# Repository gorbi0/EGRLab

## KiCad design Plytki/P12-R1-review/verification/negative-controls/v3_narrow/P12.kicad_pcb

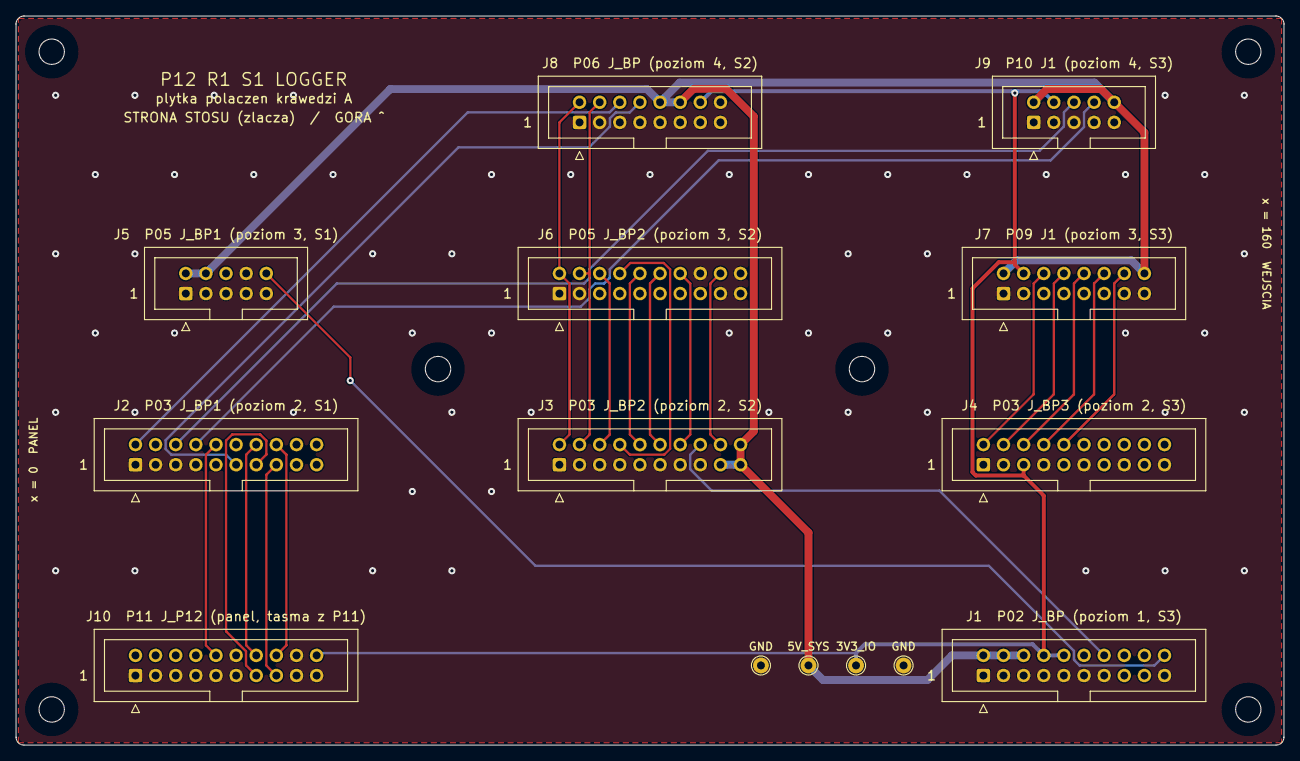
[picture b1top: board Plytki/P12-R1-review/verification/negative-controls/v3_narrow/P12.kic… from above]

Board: 2 copper layers, 160.0 x 92.0 mm, 20 parts (0 on the bottom side), 27 nets.

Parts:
H1, H2, H3, H4, H5, H6: M3 NPTH
J1: P02 J_BP; IDC-Header_2x10_P2.54mm_Vertical
J2: P03 J_BP1; IDC-Header_2x10_P2.54mm_Vertical
J3: P03 J_BP2; IDC-Header_2x10_P2.54mm_Vertical
J4: P03 J_BP3; IDC-Header_2x10_P2.54mm_Vertical
J5: P05 J_BP1; IDC-Header_2x05_P2.54mm_Vertical
J6: P05 J_BP2; IDC-Header_2x10_P2.54mm_Vertical
J7: P09 J1; IDC-Header_2x08_P2.54mm_Vertical
J8: P06 J_BP; IDC-Header_2x08_P2.54mm_Vertical
J9: P10 J1; IDC-Header_2x05_P2.54mm_Vertical
J10: P11 J_P12; IDC-Header_2x10_P2.54mm_Vertical
TP1, TP4: GND; TestPoint_THTPad_D2.0mm_Drill1.0mm
TP2: 5V_SYS; TestPoint_THTPad_D2.0mm_Drill1.0mm
TP3: 3V3_IO; TestPoint_THTPad_D2.0mm_Drill1.0mm

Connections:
3V3_IO: J1.8, J1.10, J4.5, J7.4, J8.14, J9.4, J10.20, TP3.1
5V_SYS: J1.2, J1.4, J1.6, J3.17, J3.19, J3.20, J5.2, J5.4, J7.2, J7.16, J8.10, J8.12, J9.2, J9.10, TP2.1
ADC_BUSY: J3.12, J6.12
ADC_CONVST: J3.10, J6.10
ADC_CS: J3.8, J6.8
ADC_DOUTA: J3.4, J6.4, J8.4
ADC_RESET: J3.18, J6.18
ADC_SCLK: J3.2, J6.2, J8.2
ADC_SDI: J3.6, J6.6
CAN_RX: J2.8, J9.8
CAN_TX: J2.6, J9.6
CS_ILOG_N: J2.2, J8.6
GND: J1.1, J1.3, J1.5, J1.7, J1.9, J1.11, J1.13, J1.19, J2.1, J2.3, J2.5, J2.7, J2.9, J3.1, J3.3, J3.5, J3.7, J3.9, J3.11, J3.13, J3.15, J4.1, J4.3, J4.7, J4.11, J4.15, J4.19, J5.1, J5.3, J5.5, J5.7, J5.8, J5.9, J6.1, J6.3, J6.5, J6.7, J6.9, J6.11, J6.13, J6.15, J6.16, J6.17, J6.19, J6.20, J7.1, J7.3, J7.5, J7.7, J7.9, J7.11, J7.13, J7.15, J8.1, J8.3, J8.5, J8.7, J8.9, J8.11, J8.13, J8.15, J8.16, J9.1, J9.3, J9.5, J9.7, J9.9, J10.1, J10.3, J10.5, J10.7, J10.9, J10.11, J10.12, J10.17, J10.18, J10.19, TP1.1, TP4.1
LOGGER_CLEAR: J2.15, J10.15
LOGGER_CURRENT_OK: J2.11, J8.8
MARK: J2.13, J10.13
MEAS_EN: J3.14, J6.14
N_J_SCOPE_HOT: J2.10, J10.10
PFAIL_N: J1.14, J3.16
SPI3_MISO: J4.6, J7.10
SPI3_MOSI: J4.4, J7.8
SPI3_SCLK: J4.2, J7.6
TC1_CS: J4.8, J7.12
TC2_CS: J4.10, J7.14
TEST_KEY: J2.14, J10.14
TEST_PRESENT: J2.16, J10.16
VBAT_SENSE: J1.20, J5.10

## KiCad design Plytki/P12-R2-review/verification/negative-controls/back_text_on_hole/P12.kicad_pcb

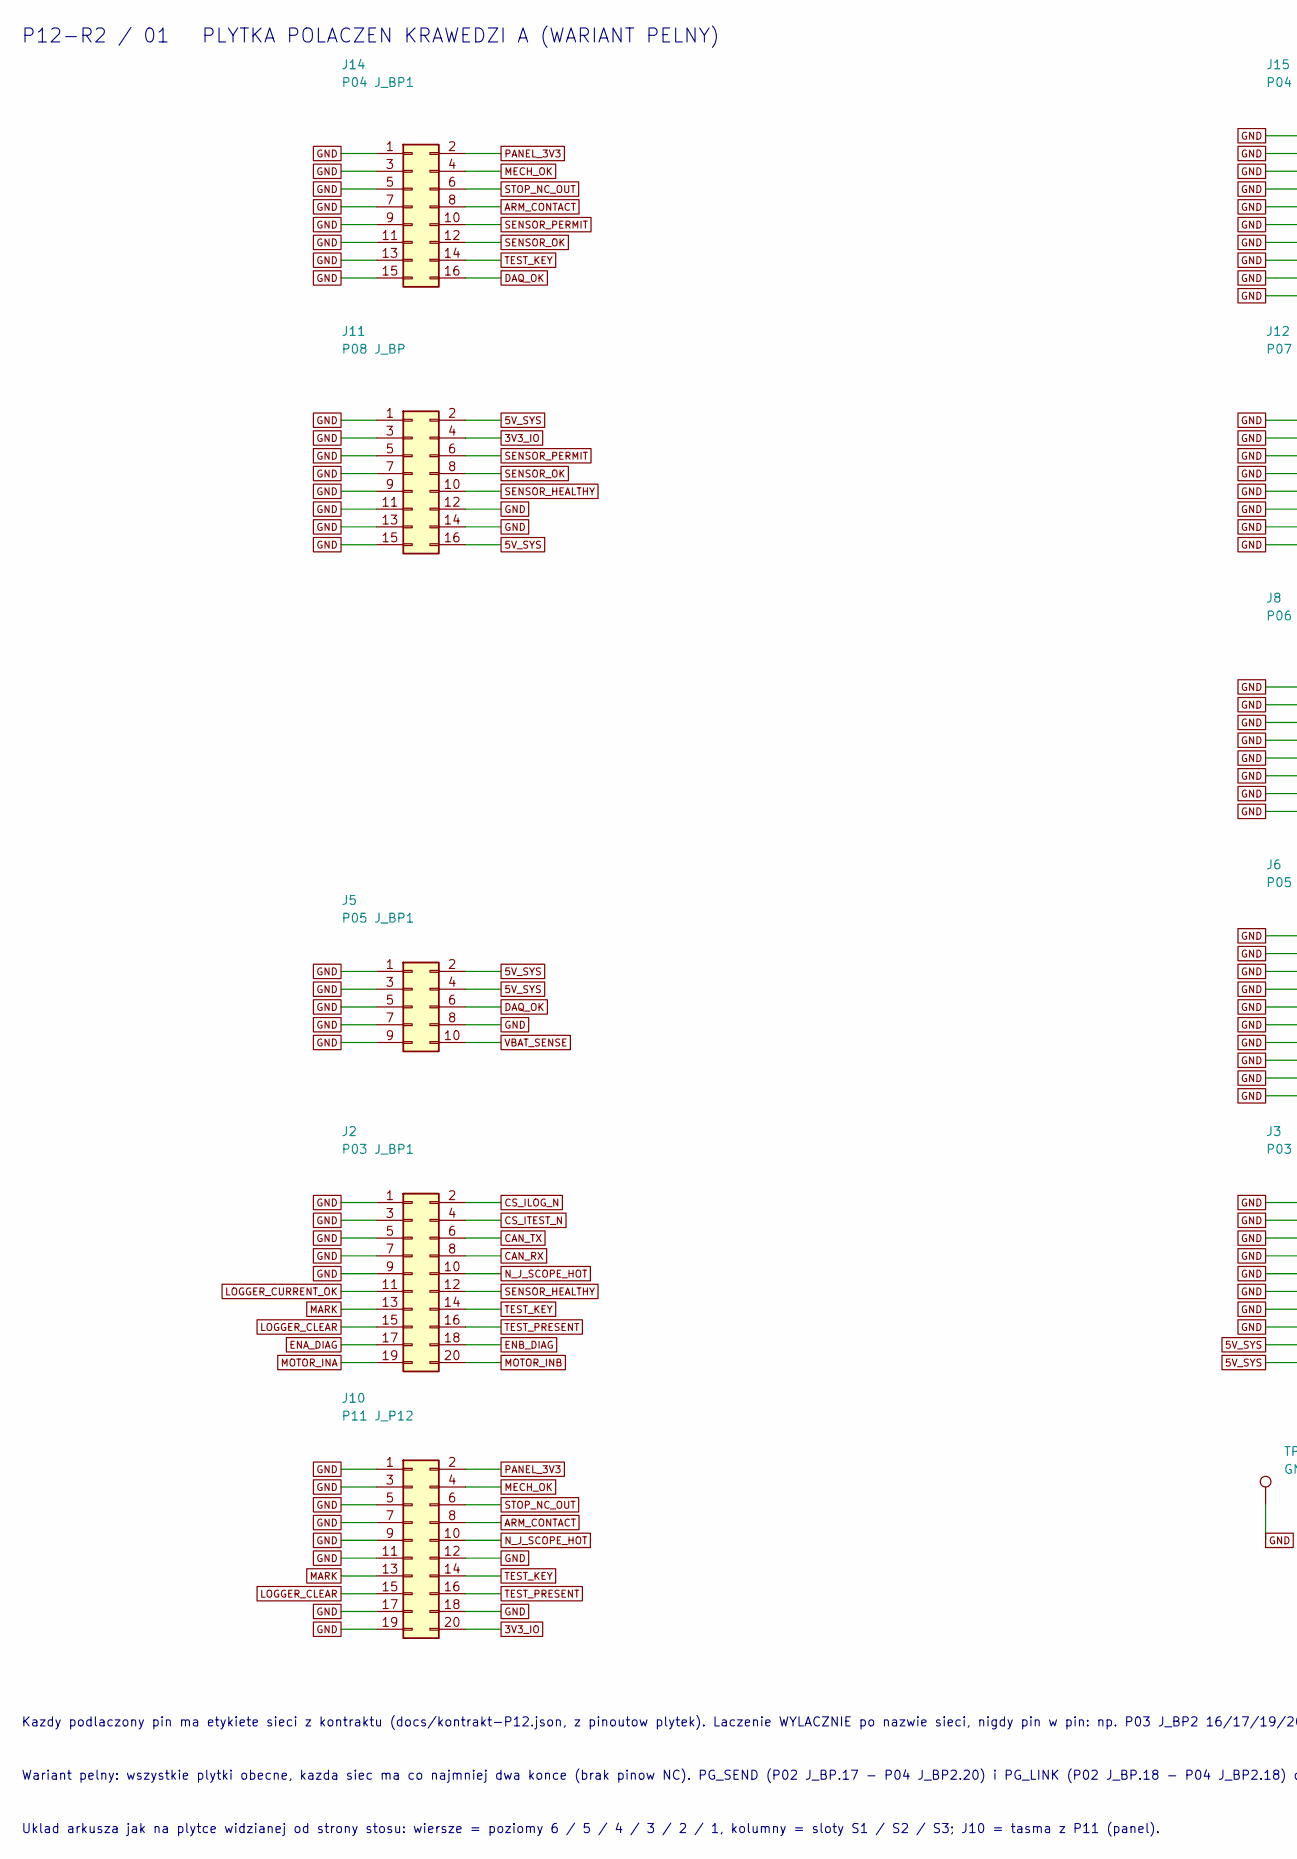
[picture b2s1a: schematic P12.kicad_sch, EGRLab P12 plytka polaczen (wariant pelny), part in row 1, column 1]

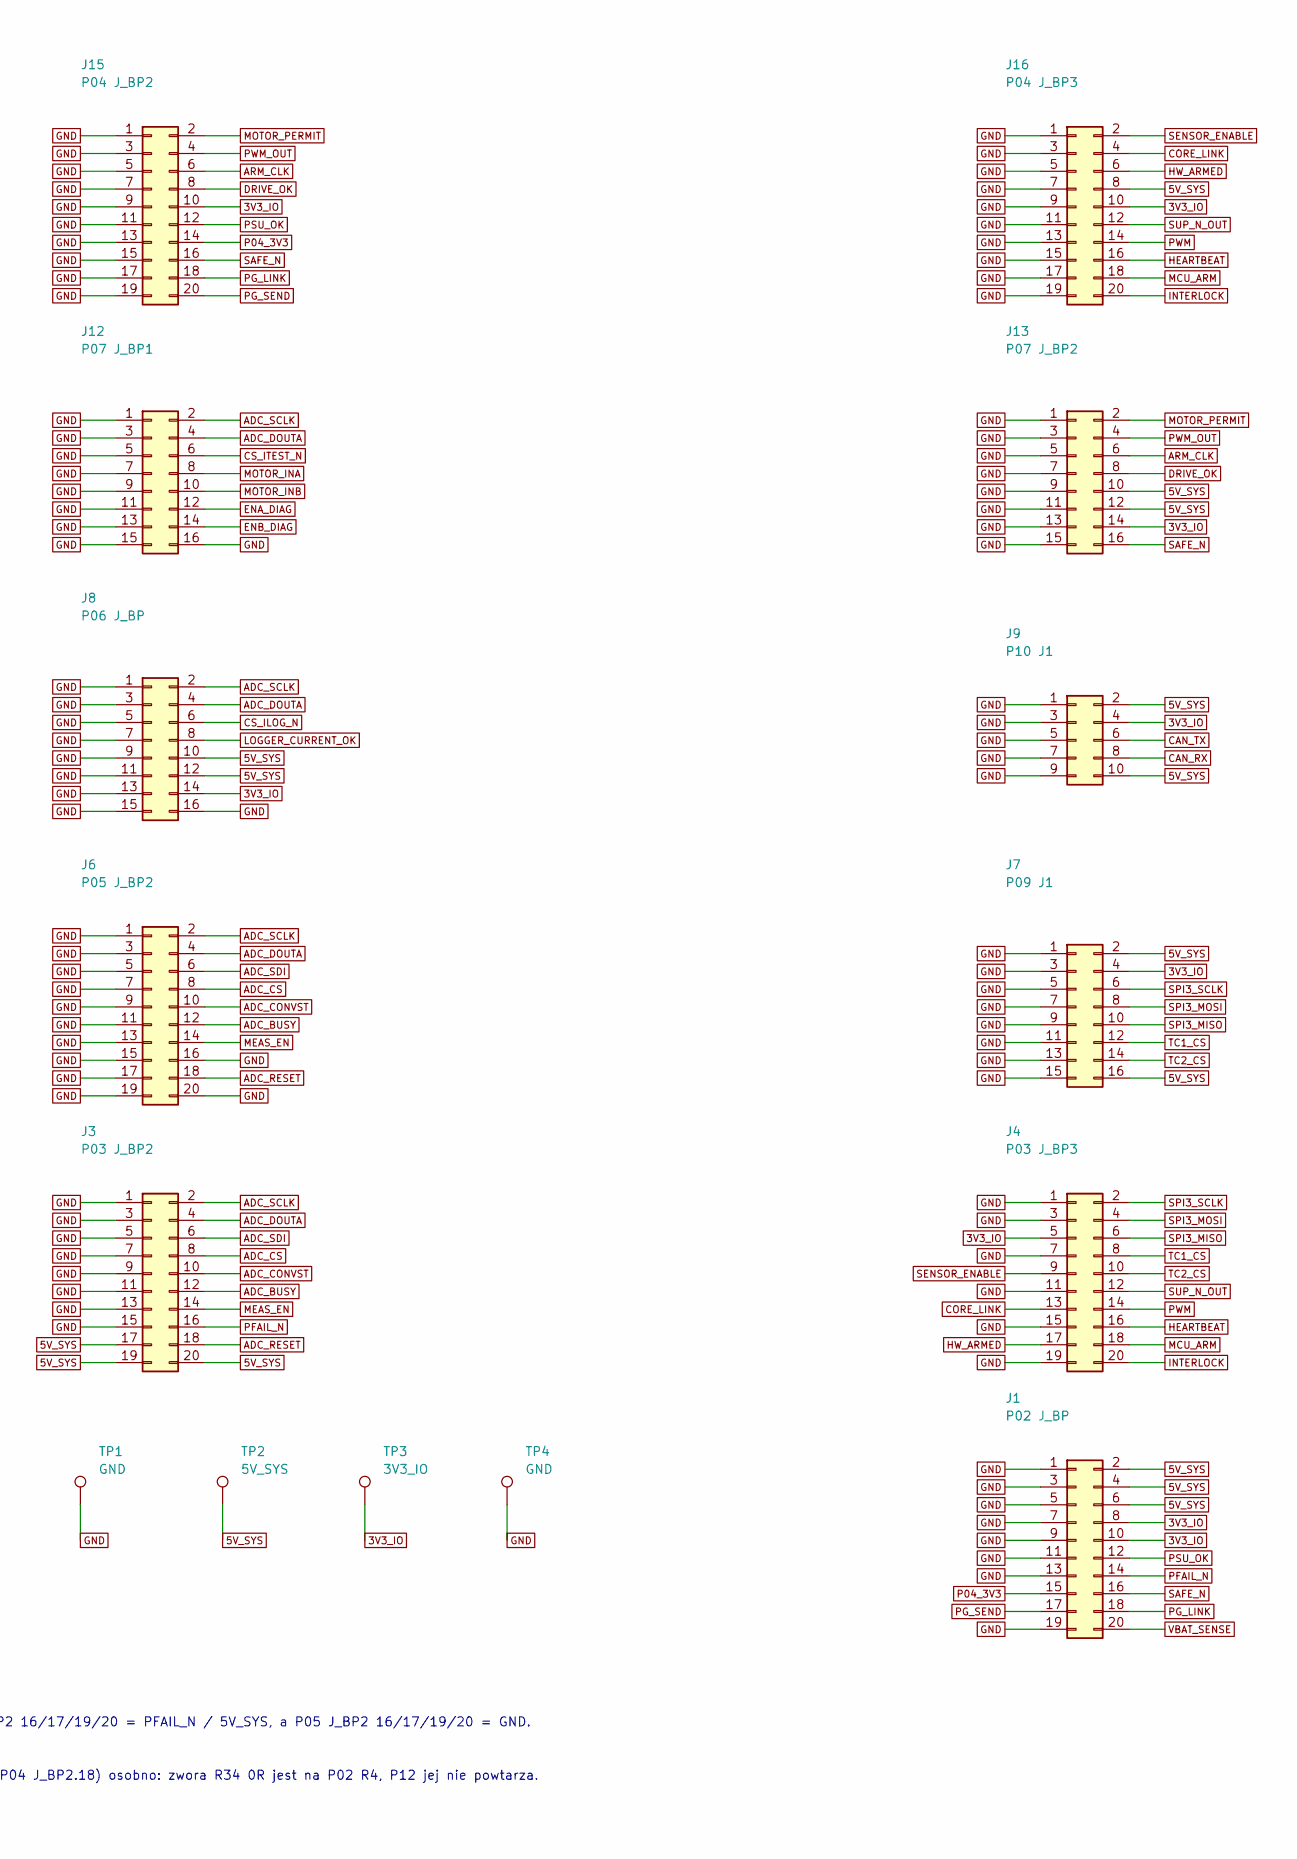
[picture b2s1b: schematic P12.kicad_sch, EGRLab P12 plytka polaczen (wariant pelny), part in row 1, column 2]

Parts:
J1: P02 J_BP; IDC-Header_2x10_P2.54mm_Vertical; MPN Amphenol FCI T821120A1S100CEU (IDC 2x10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
J2: P03 J_BP1; IDC-Header_2x10_P2.54mm_Vertical; MPN Amphenol FCI T821120A1S100CEU (IDC 2x10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
J3: P03 J_BP2; IDC-Header_2x10_P2.54mm_Vertical; MPN Amphenol FCI T821120A1S100CEU (IDC 2x10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
J4: P03 J_BP3; IDC-Header_2x10_P2.54mm_Vertical; MPN Amphenol FCI T821120A1S100CEU (IDC 2x10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
J5: P05 J_BP1; IDC-Header_2x05_P2.54mm_Vertical; MPN Amphenol FCI T821110A1S100CEU (IDC 2x5 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
J6: P05 J_BP2; IDC-Header_2x10_P2.54mm_Vertical; MPN Amphenol FCI T821120A1S100CEU (IDC 2x10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
J7: P09 J1; IDC-Header_2x08_P2.54mm_Vertical; MPN Amphenol FCI T821116A1S100CEU (IDC 2x8 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
J8: P06 J_BP; IDC-Header_2x08_P2.54mm_Vertical; MPN Amphenol FCI T821116A1S100CEU (IDC 2x8 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
J9: P10 J1; IDC-Header_2x05_P2.54mm_Vertical; MPN Amphenol FCI T821110A1S100CEU (IDC 2x5 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
J10: P11 J_P12; IDC-Header_2x10_P2.54mm_Vertical; MPN Amphenol FCI T821120A1S100CEU (IDC 2x10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
J11: P08 J_BP; IDC-Header_2x08_P2.54mm_Vertical; MPN Amphenol FCI T821116A1S100CEU (IDC 2x8 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
J12: P07 J_BP1; IDC-Header_2x08_P2.54mm_Vertical; MPN Amphenol FCI T821116A1S100CEU (IDC 2x8 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
J13: P07 J_BP2; IDC-Header_2x08_P2.54mm_Vertical; MPN Amphenol FCI T821116A1S100CEU (IDC 2x8 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
J14: P04 J_BP1; IDC-Header_2x08_P2.54mm_Vertical; MPN Amphenol FCI T821116A1S100CEU (IDC 2x8 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
J15: P04 J_BP2; IDC-Header_2x10_P2.54mm_Vertical; MPN Amphenol FCI T821120A1S100CEU (IDC 2x10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
J16: P04 J_BP3; IDC-Header_2x10_P2.54mm_Vertical; MPN Amphenol FCI T821120A1S100CEU (IDC 2x10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
TP1, TP4: GND; TestPoint_THTPad_D2.0mm_Drill1.0mm; MPN pole pomiarowe THT D2,0 / otwór 1,0 (be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
TP2: 5V_SYS; TestPoint_THTPad_D2.0mm_Drill1.0mm; MPN pole pomiarowe THT D2,0 / otwór 1,0 (be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
TP3: 3V3_IO; TestPoint_THTPad_D2.0mm_Drill1.0mm; MPN pole pomiarowe THT D2,0 / otwór 1,0 (be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

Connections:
3V3_IO: J1.8, J1.10, J4.5, J7.4, J8.14, J9.4, J10.20, J11.4, J13.14, J15.10, J16.10, TP3.1
5V_SYS: J1.2, J1.4, J1.6, J3.17, J3.19, J3.20, J5.2, J5.4, J7.2, J7.16, J8.10, J8.12, J9.2, J9.10, J11.2, J11.16, J13.10, J13.12, J16.8, TP2.1
ADC_BUSY: J3.12, J6.12
ADC_CONVST: J3.10, J6.10
ADC_CS: J3.8, J6.8
ADC_DOUTA: J3.4, J6.4, J8.4, J12.4
ADC_RESET: J3.18, J6.18
ADC_SCLK: J3.2, J6.2, J8.2, J12.2
ADC_SDI: J3.6, J6.6
ARM_CLK: J13.6, J15.6
ARM_CONTACT: J10.8, J14.8
CAN_RX: J2.8, J9.8
CAN_TX: J2.6, J9.6
CORE_LINK: J4.13, J16.4
CS_ILOG_N: J2.2, J8.6
CS_ITEST_N: J2.4, J12.6
DAQ_OK: J5.6, J14.16
DRIVE_OK: J13.8, J15.8
ENA_DIAG: J2.17, J12.12
ENB_DIAG: J2.18, J12.14
GND: J1.1, J1.3, J1.5, J1.7, J1.9, J1.11, J1.13, J1.19, J2.1, J2.3, J2.5, J2.7, J2.9, J3.1, J3.3, J3.5, J3.7, J3.9, J3.11, J3.13, J3.15, J4.1, J4.3, J4.7, J4.11, J4.15, J4.19, J5.1, J5.3, J5.5, J5.7, J5.8, J5.9, J6.1, J6.3, J6.5, J6.7, J6.9, J6.11, J6.13, J6.15, J6.16, J6.17, J6.19, J6.20, J7.1, J7.3, J7.5, J7.7, J7.9, J7.11, J7.13, J7.15, J8.1, J8.3, J8.5, J8.7, J8.9, J8.11, J8.13, J8.15, J8.16, J9.1, J9.3, J9.5, J9.7, J9.9, J10.1, J10.3, J10.5, J10.7, J10.9, J10.11, J10.12, J10.17, J10.18, J10.19, J11.1, J11.3, J11.5, J11.7, J11.9, J11.11, J11.12, J11.13, J11.14, J11.15, J12.1, J12.3, J12.5, J12.7, J12.9, J12.11, J12.13, J12.15, J12.16, J13.1, J13.3, J13.5, J13.7, J13.9, J13.11, J13.13, J13.15, J14.1, J14.3, J14.5, J14.7, J14.9, J14.11, J14.13, J14.15, J15.1, J15.3, J15.5, J15.7, J15.9, J15.11, J15.13, J15.15, J15.17, J15.19, J16.1, J16.3, J16.5, J16.7, J16.9, J16.11, J16.13, J16.15, J16.17, J16.19, TP1.1, TP4.1
HEARTBEAT: J4.16, J16.16
HW_ARMED: J4.17, J16.6
INTERLOCK: J4.20, J16.20
LOGGER_CLEAR: J2.15, J10.15
LOGGER_CURRENT_OK: J2.11, J8.8
MARK: J2.13, J10.13
MCU_ARM: J4.18, J16.18
MEAS_EN: J3.14, J6.14
MECH_OK: J10.4, J14.4
MOTOR_INA: J2.19, J12.8
MOTOR_INB: J2.20, J12.10
MOTOR_PERMIT: J13.2, J15.2
N_J_SCOPE_HOT: J2.10, J10.10
P04_3V3: J1.15, J15.14
PANEL_3V3: J10.2, J14.2
PFAIL_N: J1.14, J3.16
PG_LINK: J1.18, J15.18
PG_SEND: J1.17, J15.20
PSU_OK: J1.12, J15.12
PWM: J4.14, J16.14
PWM_OUT: J13.4, J15.4
SAFE_N: J1.16, J13.16, J15.16
SENSOR_ENABLE: J4.9, J16.2
SENSOR_HEALTHY: J2.12, J11.10
SENSOR_OK: J11.8, J14.12
SENSOR_PERMIT: J11.6, J14.10
SPI3_MISO: J4.6, J7.10
SPI3_MOSI: J4.4, J7.8
SPI3_SCLK: J4.2, J7.6
STOP_NC_OUT: J10.6, J14.6
SUP_N_OUT: J4.12, J16.12
TC1_CS: J4.8, J7.12
TC2_CS: J4.10, J7.14
TEST_KEY: J2.14, J10.14, J14.14
TEST_PRESENT: J2.16, J10.16
VBAT_SENSE: J1.20, J5.10

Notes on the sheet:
Kazdy podlaczony pin ma etykiete sieci z kontraktu (docs/kontrakt-P12.json, z pinoutow plytek). Laczenie WYLACZNIE po nazwie sieci, nigdy pin w pin: np. P03 J_BP2 16/17/19/20 = PFAIL_N / 5V_SYS, a P05 J_BP2 16/17/19/20 = GND.
Wariant pelny: wszystkie plytki obecne, kazda siec ma co najmniej dwa konce (brak pinow NC). PG_SEND (P02 J_BP.17 - P04 J_BP2.20) i PG_LINK (P02 J_BP.18 - P04 J_BP2.18) osobno: zwora R34 0R jest na P02 R4, P12 jej nie powtarza.
Uklad arkusza jak na plytce widzianej od strony stosu: wiersze = poziomy 6 / 5 / 4 / 3 / 2 / 1, kolumny = sloty S1 / S2 / S3; J10 = tasma z P11 (panel).
P12-R2 / 01 PLYTKA POLACZEN KRAWEDZI A (WARIANT PELNY)

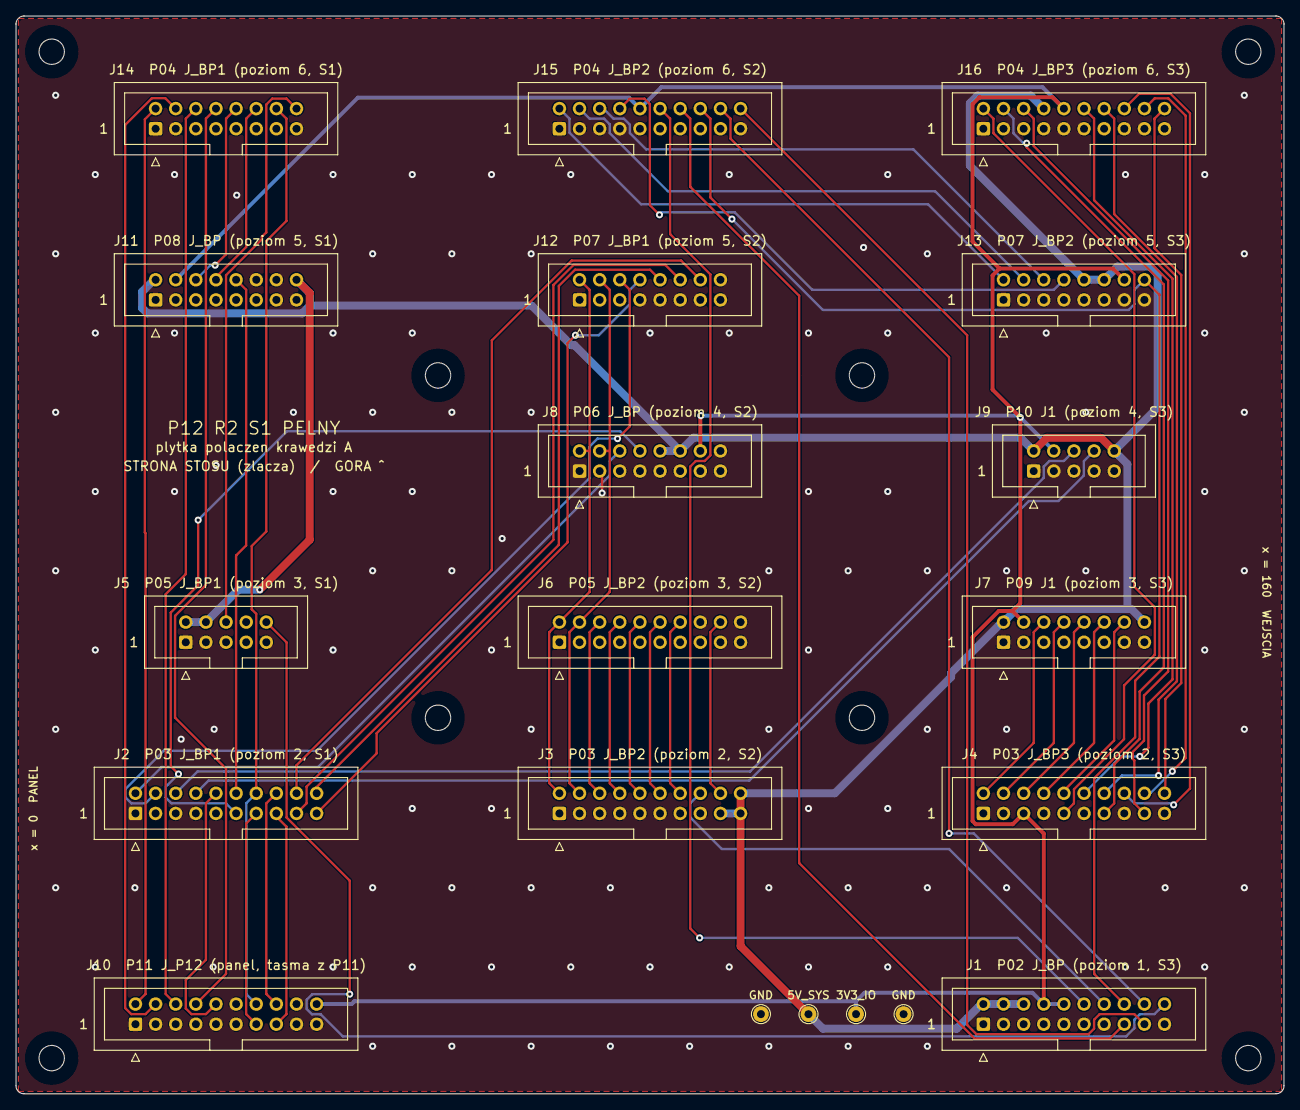
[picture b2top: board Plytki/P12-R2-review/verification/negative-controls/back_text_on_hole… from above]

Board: 2 copper layers, 160.0 x 136.0 mm, 28 parts (0 on the bottom side), 57 nets.

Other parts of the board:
H1, H2, H3, H4, H5, H6, H7, H8: M3 NPTH
